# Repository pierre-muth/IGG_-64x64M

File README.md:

# IGG_-64x64M
Driving and use the ИГГ1/64x64M. Gazotron Dot-matrix display made in Ukraine in the 80's
Details: https://hackaday.io/project/46302-1-64x64m-adventure

Status:
High voltage (360v from 180v) driver circuit board
PIC 18F87K90 serial interface

Connected to a raspberry-pi: https://youtu.be/ZqoKS0ZieYE

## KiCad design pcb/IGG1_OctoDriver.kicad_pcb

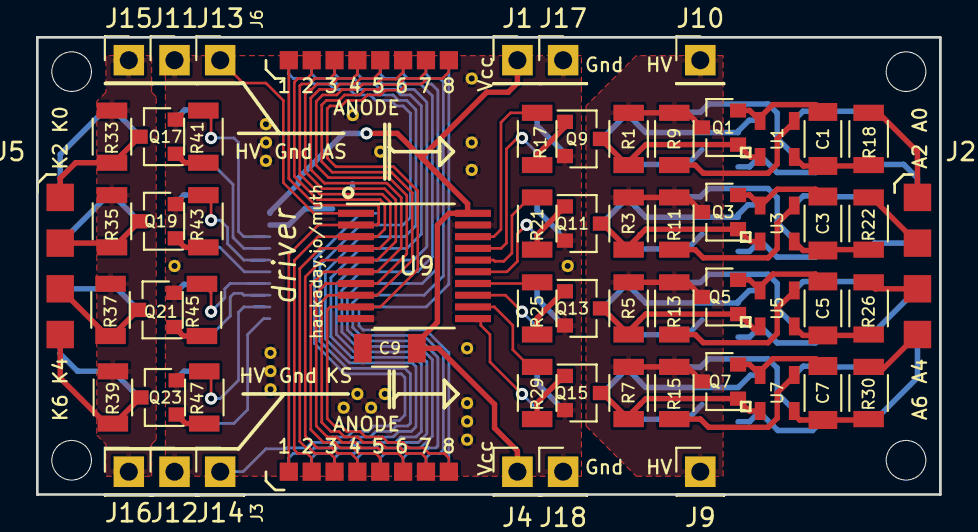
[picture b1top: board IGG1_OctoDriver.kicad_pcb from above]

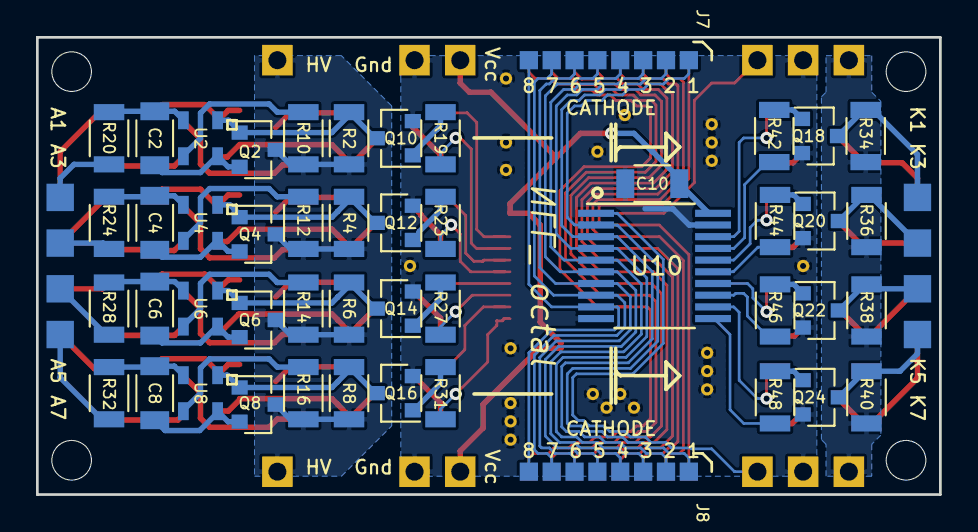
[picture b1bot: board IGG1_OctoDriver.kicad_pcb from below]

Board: 2 copper layers, 50.2 x 25.4 mm, 131 parts (48 on the bottom side), 101 nets.

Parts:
C1, C2, C3, C4, C5, C6, C7, C8: 1n; C_1206
C9, C10: 100n; C_1206
J1, J4, J9, J10, J11, J12, J13, J14, J15, J16, J17, J18: Conn_01x01; Pin_Header_Straight_1x01_Pitch2.54mm
J2, J5: Conn_01x08; Pin_Header_21x04_Pitch2.54mm_SMD_2sides
J3, J6, J7, J8: Conn_01x08; Pin_Header_1x08_Pitch1.27mm_SMD
J19, J19#2, J19#3, J19#4, J19#5, J19#6, J19#7, J19#8, J19#9, J19#10, J19#11, J19#12, J19#13, J19#14, J19#15, J19#16, J19#17, J19#18, J19#19, J19#20, J19#21: TEST_1P; via
Q1, Q2, Q3, Q4, Q5, Q6, Q7, Q8, Q9, Q10, Q11, Q12, Q13, Q14, Q15, Q16, Q17, Q18, Q19, Q20, Q21, Q22, Q23, Q24: Q_NPN_BEC; SOT-23
R1, R2, R3, R4, R5, R6, R7, R8, R33, R34, R35, R36, R37, R38, R39, R40: 220K; R_1206
R9, R10, R11, R12, R13, R14, R15, R16: 4.7K; R_1206
R17, R19, R21, R23, R25, R27, R29, R31, R41, R42, R43, R44, R45, R46, R47, R48: 10K; R_1206
R18, R20, R22, R24, R26, R28, R30, R32: 100K; R_1206
U1, U2, U3, U4, U5, U6, U7, U8: DiodeArray; SOT-457
U9, U10: 74LS541; TSSOP-20_4.4x6.5mm_Pitch0.65mm_handsoldering

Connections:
AI0: R17.2, U9.18
AI1: R19.2, U9.17
AI2: R21.2, U9.16
AI3: R23.2, U9.15
AI4: R25.2, U9.14
AI5: R27.2, U9.13
AI6: R29.2, U9.12
AI7: R31.2, U9.11
AO0: J2.1, R18.1
AO1: J2.2, R20.1
AO2: J2.3, R22.1
AO3: J2.4, R24.1
AO4: J2.5, R26.1
AO5: J2.6, R28.1
AO6: J2.7, R30.1
AO7: J2.8, R32.1
AS: J13.1, U9.1
GND: C9.1, C10.1, J11.1, J12.1, J17.1, J18.1, J19.1, J19#2.1, J19#3.1, J19#4.1, J19#5.1, J19#6.1, J19#7.1, J19#8.1, J19#9.1, J19#10.1, J19#11.1, J19#12.1, J19#13.1, J19#14.1, J19#15.1, J19#16.1, J19#17.1, J19#18.1, J19#19.1, J19#20.1, J19#21.1, Q9.2, Q10.2, Q11.2, Q12.2, Q13.2, Q14.2, Q15.2, Q16.2, Q17.2, Q18.2, Q19.2, Q20.2, Q21.2, Q22.2, Q23.2, Q24.2, U9.10, U9.19, U10.10, U10.19
HT: J9.1, J10.1, J15.1, J16.1, Q1.3, Q2.3, Q3.3, Q4.3, Q5.3, Q6.3, Q7.3, Q8.3, R1.1, R2.1, R3.1, R4.1, R5.1, R6.1, R7.1, R8.1, R9.1, R10.1, R11.1, R12.1, R13.1, R14.1, R15.1, R16.1, R33.1, R34.1, R35.1, R36.1, R37.1, R38.1, R39.1, R40.1
KI0: R41.2, U10.18
KI1: R42.2, U10.17
KI2: R43.2, U10.16
KI3: R44.2, U10.15
KI4: R45.2, U10.14
KI5: R46.2, U10.13
KI6: R47.2, U10.12
KI7: R48.2, U10.11
KO0: J5.1, Q17.3, R33.2
KO1: J5.2, Q18.3, R34.2
KO2: J5.3, Q19.3, R35.2
KO3: J5.4, Q20.3, R36.2
KO4: J5.5, Q21.3, R37.2
KO5: J5.6, Q22.3, R38.2
KO6: J5.7, Q23.3, R39.2
KO7: J5.8, Q24.3, R40.2
KS: J14.1, U10.1
unnamed: C1.1, R18.2, U1.3
unnamed: C1.2, Q1.2, U1.6
unnamed: C2.1, R20.2, U2.3
unnamed: C2.2, Q2.2, U2.6
unnamed: C3.1, R22.2, U3.3
unnamed: C3.2, Q3.2, U3.6
unnamed: C4.1, R24.2, U4.3
unnamed: C4.2, Q4.2, U4.6
unnamed: C5.1, R26.2, U5.3
unnamed: C5.2, Q5.2, U5.6
unnamed: C6.1, R28.2, U6.3
unnamed: C6.2, Q6.2, U6.6
unnamed: C7.1, R30.2, U7.3
unnamed: C7.2, Q7.2, U7.6
unnamed: C8.1, R32.2, U8.3
unnamed: C8.2, Q8.2, U8.6
unnamed: J3.1, J6.1, U9.2
unnamed: J3.2, J6.2, U9.3
unnamed: J3.3, J6.3, U9.4
unnamed: J3.4, J6.4, U9.5
unnamed: J3.5, J6.5, U9.6
unnamed: J3.6, J6.6, U9.7
unnamed: J3.7, J6.7, U9.8
unnamed: J3.8, J6.8, U9.9
unnamed: J7.1, J8.1, U10.2
unnamed: J7.2, J8.2, U10.3
unnamed: J7.3, J8.3, U10.4
unnamed: J7.4, J8.4, U10.5
unnamed: J7.5, J8.5, U10.6
unnamed: J7.6, J8.6, U10.7
unnamed: J7.7, J8.7, U10.8
unnamed: J7.8, J8.8, U10.9
unnamed: Q1.1, Q9.3, R1.2, U1.1
unnamed: Q9.1, R17.1
unnamed: Q10.1, R19.1
unnamed: Q2.1, Q10.3, R2.2, U2.1
unnamed: Q11.1, R21.1
unnamed: Q3.1, Q11.3, R3.2, U3.1
unnamed: Q12.1, R23.1
unnamed: Q4.1, Q12.3, R4.2, U4.1
unnamed: Q13.1, R25.1
unnamed: Q5.1, Q13.3, R5.2, U5.1
unnamed: Q14.1, R27.1
unnamed: Q6.1, Q14.3, R6.2, U6.1
unnamed: Q15.1, R29.1
unnamed: Q7.1, Q15.3, R7.2, U7.1
unnamed: Q16.1, R31.1
unnamed: Q8.1, Q16.3, R8.2, U8.1
unnamed: Q17.1, R41.1
unnamed: Q18.1, R42.1
unnamed: Q19.1, R43.1
unnamed: Q20.1, R44.1
unnamed: Q21.1, R45.1
unnamed: Q22.1, R46.1
unnamed: Q23.1, R47.1
unnamed: Q24.1, R48.1
unnamed: R9.2, U1.4
unnamed: R10.2, U2.4
unnamed: R11.2, U3.4
unnamed: R12.2, U4.4
unnamed: R13.2, U5.4
unnamed: R14.2, U6.4
unnamed: R15.2, U7.4
unnamed: R16.2, U8.4
VCC: C9.2, C10.2, J1.1, J4.1, U9.20, U10.20

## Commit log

2018-02-09 add kicad file
2018-02-14 extract driver kicad files to pcb folder
2018-02-14 Update status on readme.
2018-03-09 Add PIC and Java code
2018-03-22 minor changes
2018-03-24 Adafruit's Pixel Dust java port test
2018-03-24 Start adding comments
2018-04-09 PIC driver at 60Hz
2018-04-09 links update
